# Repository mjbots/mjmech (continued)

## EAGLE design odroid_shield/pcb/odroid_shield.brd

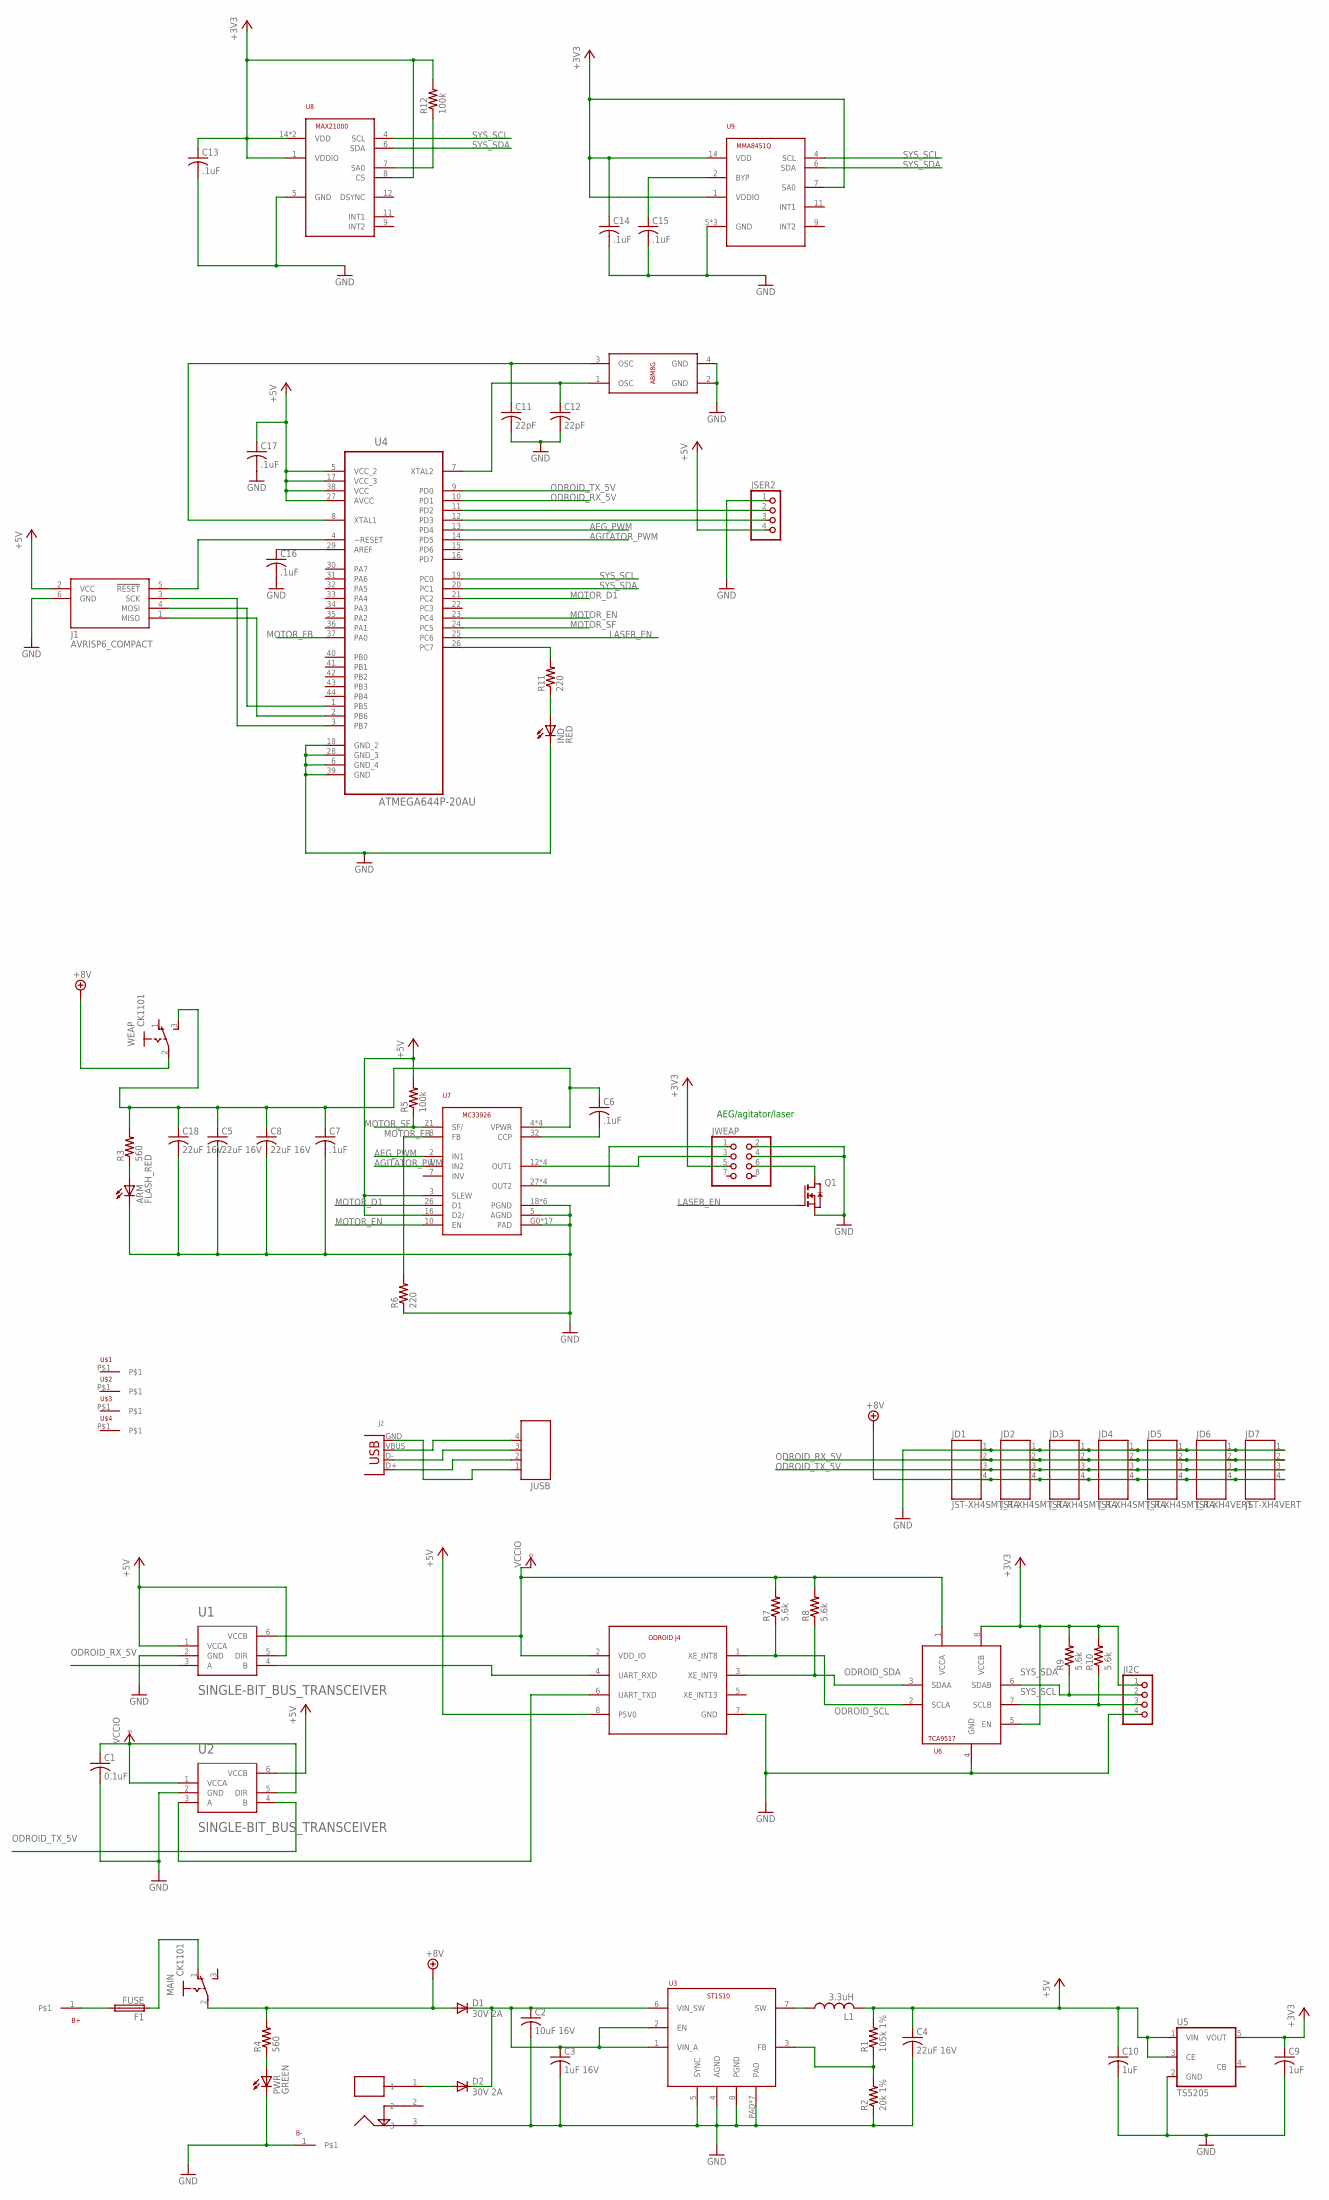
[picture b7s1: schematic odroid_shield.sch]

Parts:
ARM: FLASH_RED; LED5MM
B+: BAT_TERM
B-: BAT_TERM
C1: 0.1uF; C0603
C2: 10uF 16V; C1206
C3: 1uF 16V; C0603
C4, C5, C8, C18: 22uF 16V; C1210
C6, C7, C13, C14, C15, C16, C17: .1uF; C0603
C9, C10: 1uF; C0603
C11, C12: 22pF; C0603
D1, D2: 30V 2A; CMS06
F1: FUSE; KEYSTONE_HORIZ_FUSE_CLIP
IND: RED; CHIPLED_0805
J1: AVRISP6_COMPACT; CON6P2R
J2: USB2MM; 1X04/2MM
J4: ODROID_J4; 2X04/2MM
JD1, JD2, JD3, JD4, JD5: JST-XH4SMT_RA; JST_XH_SMT_RA_4
JD6, JD7: JST-XH4VERT; JST_XH_VERT_4
JI2C: PINHD-1X4; 1X04
JSER2: PINHD-1X4; 1X04
JUSB: JST-PH4
JWEAP: PINHD-2X4; 2X04
L1: 3.3uH; WURTH_74404042033
MAIN: CK1101; CK1101C
PWR: GREEN; CHIPLED_0805
Q1: NMOSSOT23; SOT-23
R1: 105k 1%; R0603
R2: 20k 1%; R0603
R3, R4: 560; R0603
R5, R12: 100k; R0603
R6, R11: 220; R0603
R7, R8, R9, R10: 5.6k; R0603
SHORE: PJ-034ASMT; CUI_PJ_015AH_SMT
U1, U2: SINGLE-BIT_BUS_TRANSCEIVER; SOT23-6
U3: ST1S10; POWER_SO8
U4: ATMEGA644P-20AU; QFP80P1200X1200X120-44N
U5: TS5205; SOT25
U6: TCA9517MSOP8; MSOP8
U7: MC33926; PQFN32
U8: MAX21000; LGA16
U9: MMA8451Q; QFN16
U10: ABM8G
U$1, U$2, U$3, U$4: M3_HEX_MOUNT
WEAP: CK1101; CK1101C

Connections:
+3V3: C9.1, C13.1, C14.1, JI2C.1, JWEAP.5, R9.2, R10.2, R12.2, U5.5 (VOUT), U6.5 (EN), U6.8 (VCCB), U8.1 (VDDIO), U8.8 (CS), U8.14 (VDD), U8.15 (VDD), U9.1 (VDDIO), U9.7 (SA0), U9.14 (VDD)
+5V: C4.1, C10.1, C17.1, J1.2 (VCC), J4.8 (P5V0), JSER2.4, L1.2, R1.2, R5.2, U1.1 (VCCA), U1.5 (DIR), U2.6 (VCCB), U4.5 (VCC_2), U4.17 (VCC_3), U4.27 (AVCC), U4.38 (VCC), U5.1 (VIN), U5.3 (CE), U7.3 (SLEW), U7.16 (D2/)
+8V: D1.1 (A), JD1.4, JD2.4, JD3.4, JD4.4, JD5.4, JD6.4, JD7.4, MAIN.2, R4.2, WEAP.2
AEG_PWM: U4.13 (PD4), U7.2 (IN1)
AGITATOR_PWM: U4.14 (PD5), U7.1 (IN2)
GND: ARM.K (C), B-.1, C1.2, C2.2, C3.2, C4.2, C5.2, C7.2, C8.2, C9.2, C10.2, C11.2, C12.2, C13.2, C14.2, C15.2, C16.2, C17.2, C18.2, IND.C, J1.6 (GND), J4.7 (GND), JD1.1, JD2.1, JD3.1, JD4.1, JD5.1, JD6.1, JD7.1, JI2C.4, JSER2.1, JWEAP.2, JWEAP.4, PWR.C, Q1.2 (S), R2.1, R6.1, SHORE.3, U1.2 (GND), U2.2 (GND), U3.4 (AGND), U3.5 (SYNC), U3.8 (PGND), U3.PAD, U3.PAD1 (PAD), U3.PAD2 (PAD), U3.PAD3 (PAD), U3.PAD4 (PAD), U3.PAD5 (PAD), U3.PAD6 (PAD), U4.6 (GND_4), U4.18 (GND_2), U4.28 (GND_3), U4.39 (GND), U5.2 (GND), U6.4 (GND), U7.5 (AGND), U7.18 (PGND), U7.19 (PGND), U7.20 (PGND), U7.22 (PGND), U7.23 (PGND), U7.24 (PGND), U7.G0 (PAD), U7.G1 (PAD), U7.G2 (PAD), U7.G3 (PAD), U7.G4 (PAD), U7.G5 (PAD), U7.G6 (PAD), U7.G7 (PAD), U7.G8 (PAD), U7.G9 (PAD), U7.G10 (PAD), U7.G11 (PAD), U7.G12 (PAD), U7.G13 (PAD), U7.G14 (PAD), U7.G15 (PAD), U7.G16 (PAD), U8.5 (GND), U9.5 (GND), U9.10 (GND), U9.12 (GND), U10.2 (GND), U10.4 (GND)
LASER_EN: Q1.3 (G), U4.25 (PC6)
MOTOR_D1: U4.21 (PC2), U7.26 (D1)
MOTOR_EN: U4.23 (PC4), U7.10 (EN)
MOTOR_FB: R6.2, U4.37 (PA0), U7.8 (FB)
MOTOR_SF: R5.1, U4.24 (PC5), U7.21 (SF/)
unnamed: J2.VBUS, JUSB.4
unnamed: J4.4 (UART_RXD), U1.4 (B)
unnamed: J2.D-, JUSB.3
unnamed: J4.6 (UART_TXD), U2.3 (A)
unnamed: J2.D+, JUSB.2
unnamed: J2.GND, JUSB.1
unnamed: B+.1, F1.3 (2), F1.4 (2)
unnamed: F1.1, F1.2 (1), MAIN.1 (O)
unnamed: D2.1 (A), SHORE.1
unnamed: L1.1, U3.7 (SW)
unnamed: C2.1, C3.1, D1.2 (C), D2.2 (C), U3.1 (VIN_A), U3.2 (EN), U3.6 (VIN_SW)
unnamed: JWEAP.1, U7.27 (OUT2), U7.28 (OUT2), U7.29 (OUT2), U7.30 (OUT2)
unnamed: R1.1, R2.2, U3.3 (FB)
unnamed: JWEAP.3, U7.12 (OUT1), U7.13 (OUT1), U7.14 (OUT1), U7.15 (OUT1)
unnamed: C5.1, C6.1, C7.1, C8.1, C18.1, R3.2, U7.4 (VPWR), U7.6 (VPWR), U7.11 (VPWR), U7.31 (VPWR), WEAP.3 (S)
unnamed: C6.2, U7.32 (CCP)
unnamed: R11.2, U4.26 (PC7)
unnamed: R12.1, U8.7 (SA0)
unnamed: JWEAP.6, Q1.1 (D)
unnamed: ARM.A, R3.1
unnamed: J1.5 (!RESET), U4.4 (~RESET)
unnamed: PWR.A, R4.1
unnamed: J1.3 (SCK), U4.3 (PB7)
unnamed: J1.4 (MOSI), U4.1 (PB5)
unnamed: J1.1 (MISO), U4.2 (PB6)
unnamed: JSER2.3, U4.12 (PD3)
unnamed: JSER2.2, U4.11 (PD2)
unnamed: IND.A, R11.1
unnamed: C16.1, U4.29 (AREF)
unnamed: C12.1, U4.7 (XTAL2), U10.1 (OSC)
unnamed: C11.1, U4.8 (XTAL1), U10.3 (OSC)
unnamed: C15.1, U9.2 (BYP)
ODROID_RX_5V: JD1.2, JD2.2, JD3.2, JD4.2, JD5.2, JD6.2, JD7.2, U1.3 (A), U4.10 (PD1)
ODROID_SCL: J4.1 (XE_INT8), R7.1, U6.2 (SCLA)
ODROID_SDA: J4.3 (XE_INT9), R8.1, U6.3 (SDAA)
ODROID_TX_5V: JD1.3, JD2.3, JD3.3, JD4.3, JD5.3, JD6.3, JD7.3, U2.4 (B), U4.9 (PD0)
SYS_SCL: JI2C.3, R10.1, U4.19 (PC0), U6.7 (SCLB), U8.4 (SCL), U9.4 (SCL)
SYS_SDA: JI2C.2, R9.1, U4.20 (PC1), U6.6 (SDAB), U8.6 (SDA), U9.6 (SDA)
VCCIO: C1.1, J4.2 (VDD_IO), R7.2, R8.2, U1.6 (VCCB), U2.1 (VCCA), U2.5 (DIR), U6.1 (VCCA)

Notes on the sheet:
AEG/agitator/laser

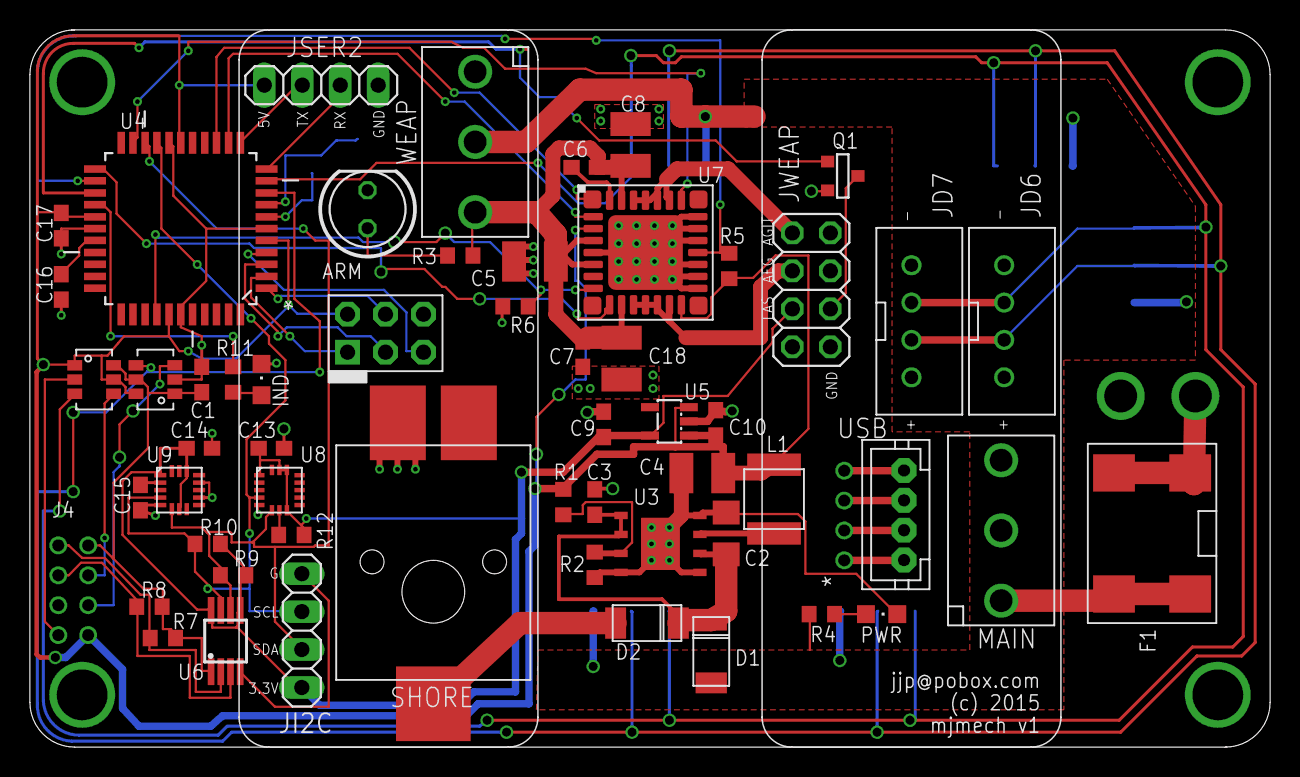
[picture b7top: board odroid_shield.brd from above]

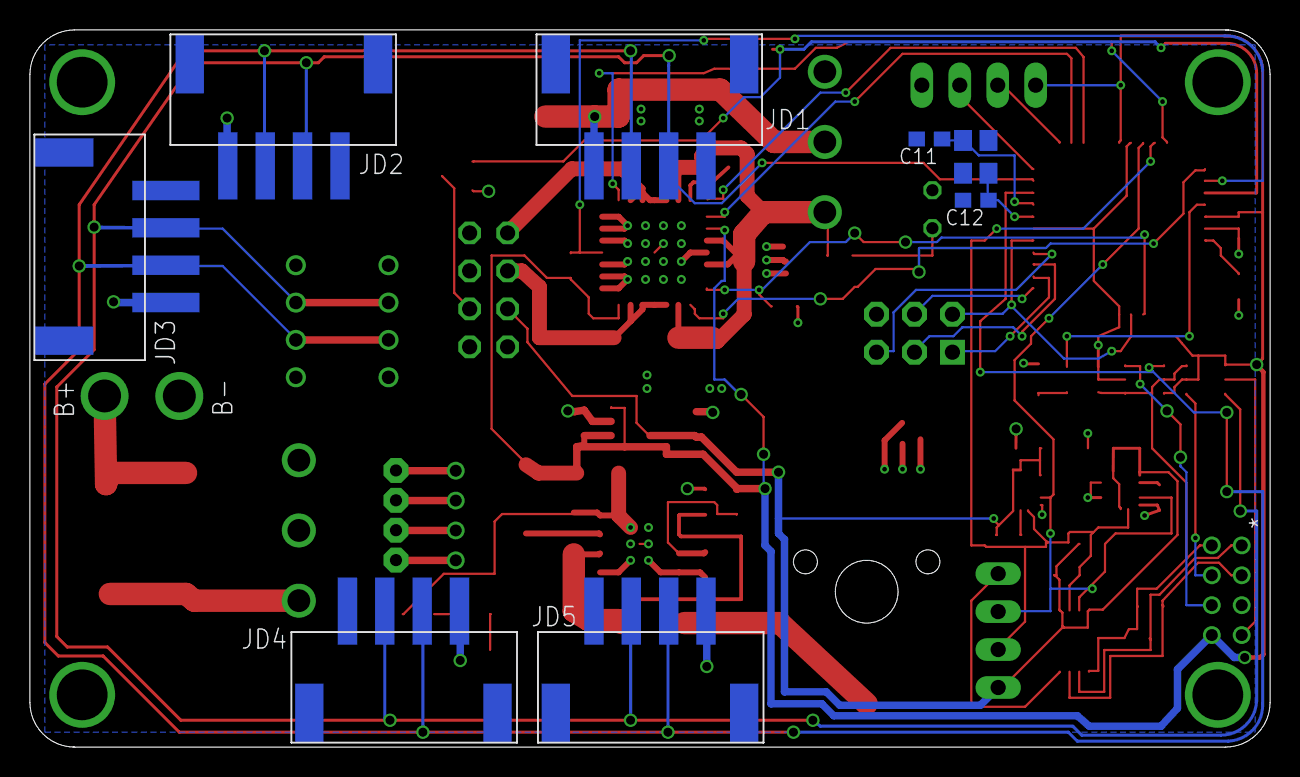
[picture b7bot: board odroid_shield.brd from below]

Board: 2 copper layers, 83.0 x 48.0 mm, 71 parts (11 on the bottom side), 50 nets.

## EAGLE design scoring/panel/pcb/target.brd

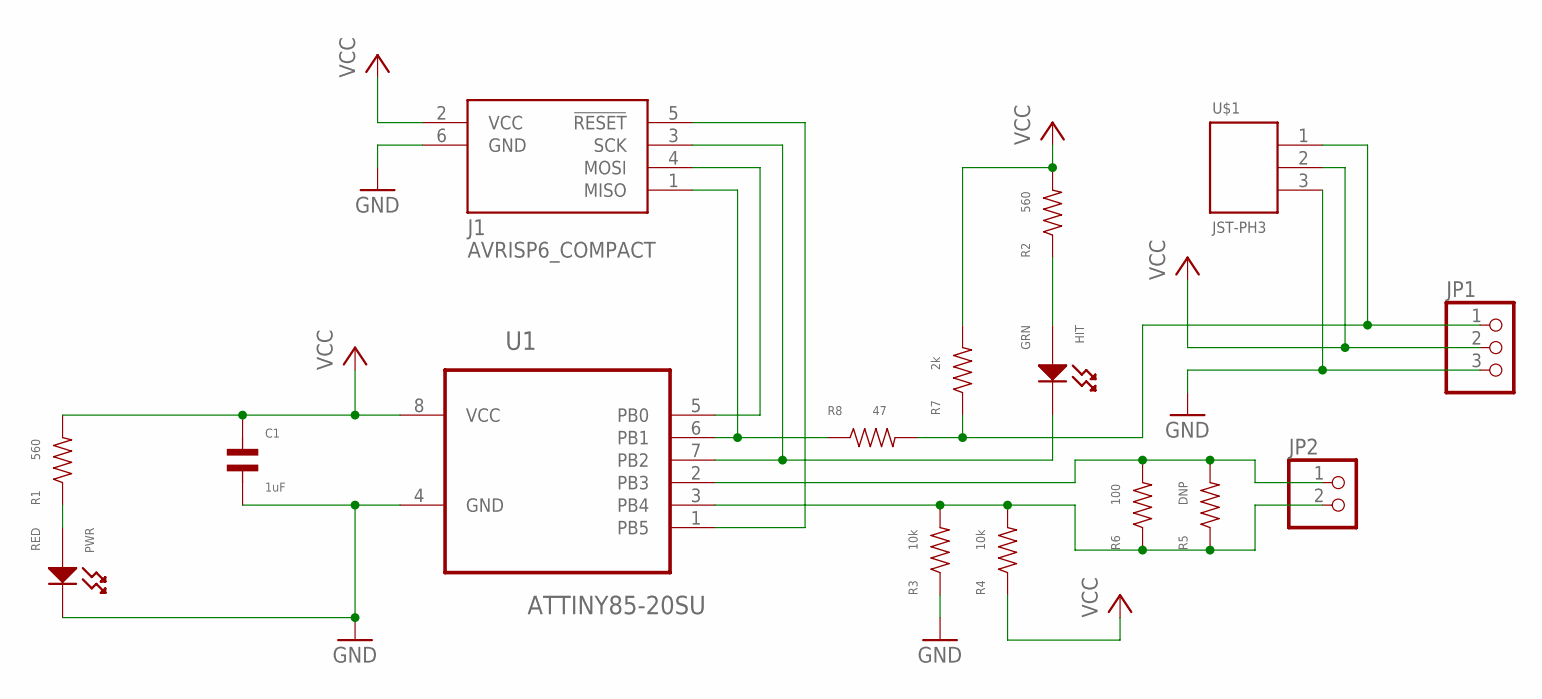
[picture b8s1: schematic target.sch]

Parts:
C1: 1uF; C0603
HIT: GRN; LED0603
J1: AVRISP6_COMPACT; CON6P2R
JP1: PINHD-1X3; 1X03
JP2: PINHD-1X2; 1X02
PWR: RED; LED0603
R1, R2: 560; R0603
R3, R4: 10k; R0603
R5: DNP; R0603
R6: 100; R0603
R7: 2k; R0603
R8: 47; R0603
U1: ATTINY85-20SU; SOIC127P798X216-8N
U$1: JST-PH3

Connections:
GND: C1.P$2, J1.6 (GND), JP1.3, PWR.CATHODE, R3.P$1, U1.4 (GND), U$1.3
unnamed: PWR.ANODE, R1.P$1
unnamed: J1.5 (!RESET), U1.1 (PB5)
unnamed: JP2.2, R3.P$2, R4.P$2, R5.P$1, R6.P$1, U1.3 (PB4)
unnamed: HIT.CATHODE, J1.3 (SCK), U1.7 (PB2)
unnamed: HIT.ANODE, R2.P$1
unnamed: JP2.1, R5.P$2, R6.P$2, U1.2 (PB3)
unnamed: J1.4 (MOSI), U1.5 (PB0)
unnamed: JP1.1, R7.P$1, R8.P$2, U$1.1
unnamed: J1.1 (MISO), R8.P$1, U1.6 (PB1)
VCC: C1.P$1, J1.2 (VCC), JP1.2, R1.P$2, R2.P$2, R4.P$1, R7.P$2, U1.8 (VCC), U$1.2

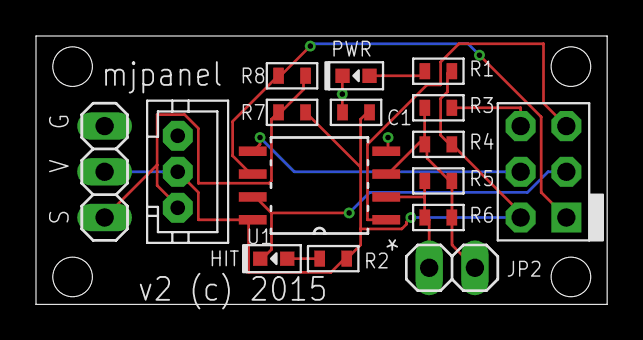
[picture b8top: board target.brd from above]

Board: 2 copper layers, 31.7 x 14.9 mm, 16 parts (0 on the bottom side), 11 nets.

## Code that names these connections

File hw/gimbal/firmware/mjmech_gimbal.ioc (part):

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Mcu.Name=STM32F411R(C-E)Tx
Mcu.Package=LQFP64
Mcu.UserName=STM32F411RETx
PA0-WKUP.Signal=S_TIM2_CH1_ETR
PA1.Signal=S_TIM2_CH2
PA10.Signal=GPIO_Output
PA11.Mode=Device_Only
PA11.Signal=USB_OTG_FS_DM
PA12.Mode=Device_Only
PA12.Signal=USB_OTG_FS_DP
PA13.Mode=Serial-Wire
PA13.Signal=SYS_JTMS-SWDIO
PA14.Mode=Serial-Wire
PA14.Signal=SYS_JTCK-SWCLK
PA15.Signal=GPIO_Input
PA2.Signal=S_TIM2_CH3
PA5.Signal=GPIO_Input
PA6.Signal=GPIO_Output
PA7.Signal=GPIO_Output
PA8.Mode=I2C
PA8.Signal=I2C3_SCL
PA9.Mode=Activate_VBUS
PA9.Signal=USB_OTG_FS_VBUS
PB0.Signal=S_TIM3_CH3
PB1.Signal=S_TIM3_CH4
PB10.Mode=I2C
PB10.Signal=I2C2_SCL
PB12.Signal=GPIO_Output
PB13.Signal=GPIO_Output
PB14.Signal=GPIO_Output
PB15.Signal=GPIO_Output
PB4.Signal=S_TIM3_CH1
PB5.Signal=S_TIM3_CH2
PB6.Mode=I2C
PB6.Signal=I2C1_SCL
PB7.Mode=I2C
PB7.Signal=I2C1_SDA
PB8.Signal=S_TIM4_CH3
PB9.Mode=I2C
PB9.Signal=I2C2_SDA
PC0.Signal=ADCx_IN10
PC1.Signal=ADCx_IN11
PC10.Mode=Full_Duplex_Master
PC10.Signal=SPI3_SCK
PC11.Mode=Full_Duplex_Master
PC11.Signal=SPI3_MISO
PC12.Mode=Full_Duplex_Master
PC12.Signal=SPI3_MOSI
PC13-ANTI_TAMP.Signal=GPIO_Output
PC14-OSC32_IN.Signal=GPIO_Output
PC15-OSC32_OUT.Signal=GPIO_Output
PC2.Signal=ADCx_IN12
PC3.Signal=GPIO_Output
PC6.Mode=Asynchronous
PC6.Signal=USART6_TX
PC7.Mode=Asynchronous
PC7.Signal=USART6_RX
PC9.Mode=I2C
PC9.Signal=I2C3_SDA
PD2.Signal=GPIO_Input
PH0\ -\ OSC_IN.Mode=HSE-External-Oscillator
PH0\ -\ OSC_IN.Signal=RCC_OSC_IN
PH1\ -\ OSC_OUT.Mode=HSE-External-Oscillator
PH1\ -\ OSC_OUT.Signal=RCC_OSC_OUT
RCC.HSE_VALUE=8000000
RCC.SYSCLKFreq_VALUE=96000000
RCC.SYSCLKSource=RCC_SYSCLKSOURCE_PLLCLK
board=mjmech_gimbal

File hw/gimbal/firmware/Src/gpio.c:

/**
  ******************************************************************************
  * File Name          : gpio.c
  * Description        : This file provides code for the configuration
  *                      of all used GPIO pins.
  ******************************************************************************
  *
  * COPYRIGHT(c) 2015 STMicroelectronics
  *
  * Redistribution and use in source and binary forms, with or without modification,
  * are permitted provided that the following conditions are met:
  *   1. Redistributions of source code must retain the above copyright notice,
  *      this list of conditions and the following disclaimer.
  *   2. Redistributions in binary form must reproduce the above copyright notice,
  *      this list of conditions and the following disclaimer in the documentation
  *      and/or other materials provided with the distribution.
  *   3. Neither the name of STMicroelectronics nor the names of its contributors
  *      may be used to endorse or promote products derived from this software
  *      without specific prior written permission.
  *
  * THIS SOFTWARE IS PROVIDED BY THE COPYRIGHT HOLDERS AND CONTRIBUTORS "AS IS"
  * AND ANY EXPRESS OR IMPLIED WARRANTIES, INCLUDING, BUT NOT LIMITED TO, THE
  * IMPLIED WARRANTIES OF MERCHANTABILITY AND FITNESS FOR A PARTICULAR PURPOSE ARE
  * DISCLAIMED. IN NO EVENT SHALL THE COPYRIGHT HOLDER OR CONTRIBUTORS BE LIABLE
  * FOR ANY DIRECT, INDIRECT, INCIDENTAL, SPECIAL, EXEMPLARY, OR CONSEQUENTIAL
  * DAMAGES (INCLUDING, BUT NOT LIMITED TO, PROCUREMENT OF SUBSTITUTE GOODS OR
  * SERVICES; LOSS OF USE, DATA, OR PROFITS; OR BUSINESS INTERRUPTION) HOWEVER
  * CAUSED AND ON ANY THEORY OF LIABILITY, WHETHER IN CONTRACT, STRICT LIABILITY,
  * OR TORT (INCLUDING NEGLIGENCE OR OTHERWISE) ARISING IN ANY WAY OUT OF THE USE
  * OF THIS SOFTWARE, EVEN IF ADVISED OF THE POSSIBILITY OF SUCH DAMAGE.
  *
  ******************************************************************************
  */

/* Includes ------------------------------------------------------------------*/
#include "gpio.h"
/* USER CODE BEGIN 0 */

/* USER CODE END 0 */

/*----------------------------------------------------------------------------*/
/* Configure GPIO                                                             */
/*----------------------------------------------------------------------------*/
/* USER CODE BEGIN 1 */

/* USER CODE END 1 */

/** Configure pins as
        * Analog
        * Input
        * Output
        * EVENT_OUT
        * EXTI
        * Free pins are configured automatically as Analog (this feature is enabled through
        * the Code Generation settings)
*/
void MX_GPIO_Init(void)
{

  GPIO_InitTypeDef GPIO_InitStruct;

  /* GPIO Ports Clock Enable */
  __GPIOC_CLK_ENABLE();
  __GPIOH_CLK_ENABLE();
  __GPIOA_CLK_ENABLE();
  __GPIOB_CLK_ENABLE();
  __GPIOD_CLK_ENABLE();

  /*Configure GPIO pins : PC13 PC14 PC15 PC3 */
  GPIO_InitStruct.Pin = GPIO_PIN_13|GPIO_PIN_14|GPIO_PIN_15|GPIO_PIN_3;
  GPIO_InitStruct.Mode = GPIO_MODE_OUTPUT_PP;
  GPIO_InitStruct.Pull = GPIO_NOPULL;
  GPIO_InitStruct.Speed = GPIO_SPEED_LOW;
  HAL_GPIO_Init(GPIOC, &GPIO_InitStruct);

  /*Configure GPIO pins : PA3 PA4 */
  GPIO_InitStruct.Pin = GPIO_PIN_3|GPIO_PIN_4;
  GPIO_InitStruct.Mode = GPIO_MODE_ANALOG;
  GPIO_InitStruct.Pull = GPIO_NOPULL;
  HAL_GPIO_Init(GPIOA, &GPIO_InitStruct);

  /*Configure GPIO pins : PA5 PA15 */
  GPIO_InitStruct.Pin = GPIO_PIN_5|GPIO_PIN_15;
  GPIO_InitStruct.Mode = GPIO_MODE_INPUT;
  GPIO_InitStruct.Pull = GPIO_NOPULL;
  HAL_GPIO_Init(GPIOA, &GPIO_InitStruct);

  /*Configure GPIO pins : PA6 PA7 PA10 */
  GPIO_InitStruct.Pin = GPIO_PIN_6|GPIO_PIN_7|GPIO_PIN_10;
  GPIO_InitStruct.Mode = GPIO_MODE_OUTPUT_PP;
  GPIO_InitStruct.Pull = GPIO_NOPULL;
  GPIO_InitStruct.Speed = GPIO_SPEED_LOW;
  HAL_GPIO_Init(GPIOA, &GPIO_InitStruct);

  /*Configure GPIO pins : PC4 PC5 PC8 */
  GPIO_InitStruct.Pin = GPIO_PIN_4|GPIO_PIN_5|GPIO_PIN_8;
  GPIO_InitStruct.Mode = GPIO_MODE_ANALOG;
  GPIO_InitStruct.Pull = GPIO_NOPULL;
  HAL_GPIO_Init(GPIOC, &GPIO_InitStruct);

  /*Configure GPIO pins : PB2 PB3 */
  GPIO_InitStruct.Pin = GPIO_PIN_2|GPIO_PIN_3;
  GPIO_InitStruct.Mode = GPIO_MODE_ANALOG;
  GPIO_InitStruct.Pull = GPIO_NOPULL;
  HAL_GPIO_Init(GPIOB, &GPIO_InitStruct);

  /*Configure GPIO pins : PB12 */
  GPIO_InitStruct.Pin = GPIO_PIN_12;
  GPIO_InitStruct.Mode = GPIO_MODE_INPUT;
  GPIO_InitStruct.Pull = GPIO_NOPULL;
  HAL_GPIO_Init(GPIOB, &GPIO_InitStruct);

  /*Configure GPIO pins : PB13 PB14 PB15 */
  GPIO_InitStruct.Pin = GPIO_PIN_12|GPIO_PIN_13|GPIO_PIN_14|GPIO_PIN_15;
  GPIO_InitStruct.Mode = GPIO_MODE_OUTPUT_PP;
  GPIO_InitStruct.Pull = GPIO_NOPULL;
  GPIO_InitStruct.Speed = GPIO_SPEED_LOW;
  HAL_GPIO_Init(GPIOB, &GPIO_InitStruct);

  /*Configure GPIO pin : PD2 */
  GPIO_InitStruct.Pin = GPIO_PIN_2;
  GPIO_InitStruct.Mode = GPIO_MODE_INPUT;
  GPIO_InitStruct.Pull = GPIO_NOPULL;
  HAL_GPIO_Init(GPIOD, &GPIO_InitStruct);

#ifdef MJMECH_DISCOVERY
  /* NOTE jpieper: These pins don't exist on the gimbal board, but are
   * connected to the LEDS on the ST discovery board. */
  GPIO_InitStruct.Pin = GPIO_PIN_12|GPIO_PIN_13|GPIO_PIN_14|GPIO_PIN_15;
  GPIO_InitStruct.Mode = GPIO_MODE_OUTPUT_PP;
  GPIO_InitStruct.Pull = GPIO_NOPULL;
  GPIO_InitStruct.Speed = GPIO_SPEED_LOW;
  HAL_GPIO_Init(GPIOD, &GPIO_InitStruct);
#endif

}

/* USER CODE BEGIN 2 */

/* USER CODE END 2 */

/**
  * @}
  */

/**
  * @}
  */

/************************ (C) COPYRIGHT STMicroelectronics *****END OF FILE****/

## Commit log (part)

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2020-04-01 Measure and report some crude metric of signal strength
2020-04-02 Display telemetry and implement minimal joystick mode
2020-04-02 Improve gait transitions
    Now, we can enter any of rest, walk, or jump, in a relatively clean
    way from the others. Leaving walk we wait for 2 gait cycles with 0
    speed.
    Update rf_command to fill in the repeat and acceleration fields so
    that jumping actually works.
2020-04-02 Make ffmpeg test actually run something
2020-04-03 Report back EAGAIN while reading
2020-04-03 Integrate video rendering into rf_command
2020-04-06 simulator: Use debug time and run at full rate
2020-04-07 Random guessing tweaks to mass and inertia
2020-04-07 Improve the jumping heuristics
    Now, we reliably switch to landing mode shortly after touching the
    ground, since we just look for displacement instead of velocity.
    Also, continually calculate a trajectory when landing so we
    semi-accurately approach the bottom of the jump. This still doesn't
    work all that well yet, so impose a minimum downward velocity also.
2020-04-16 Update config and simulator to new leg geometry
    Not built on robot yet!
2020-04-16 Stub of backflip mode
2020-04-17 aeg_driver: Route most power/gnd
2020-04-17 aeg_driver: Curate BOM
2020-04-25 Move the old turret files out of the way for now
2020-04-25 Many random 3d files for turret
2020-04-25 setup-system: Setup isolcpus and a unique SSID
2020-04-25 The very beginnings of a push stage
2020-04-25 Copy-pasta enough to record the IMU
2020-04-26 Connect up timing measurement in the turret
2020-04-26 Support changing the sign of the servos
2020-04-26 Connect up a rudimentary web_control
2020-04-26 Request higher precision info from servos
2020-04-26 Send always stopped control commands
2020-04-26 Update mjlib
2020-04-27 Beginnings of RF support for the turret
2020-04-27 Actually report the timestamp again
    This was broken by 50a5ad5443fe305bfe79968b803bc44f36e4da29
2020-04-28 Provide a cmline option to scale the max torque for each joint
2020-04-30 More turret prints
2020-04-30 Include screen in the set of utilities
2020-04-30 rf_command: Support rotating the video
2020-05-01 Limit the pitch based on the servo readout
2020-05-01 Incorporate raspicam
2020-05-01 Stub of a raspicam based camera driver
2020-05-01 Basic target tracking
2020-05-03 More turret hw
2020-05-04 Automatically start the turret software in a screen session
2020-05-04 Make the jump acceleration configurable
2020-05-04 Random turret 3d print change
2020-05-05 Use a non-linear control mapping for turret rate
2020-05-05 Tweak yaw gains
2020-05-05 Support multiple overlapping configuration files
2020-05-06 Convert quaternions back into Eigen versions
2020-05-07 Make balance use force control for stance legs
2020-05-07 Add a draft mech warfare config
2020-05-09 Switch to the docking branch of imgui
2020-05-09 tplot2: Implement arrays
2020-05-09 tplot2: Fix seeking
    Turns out std::map::insert doesn't overwrite.
2020-05-09 Make local_override work for github_archive when a `build_file` is present
2020-05-10 tplot2: Add the ability to remove plots
2020-05-10 Render unset optionals as disconnected
2020-05-10 tplot2: Set properties of individual plots
2020-05-11 Update implot
2020-05-11 Enable 32 bit indices in imgui so big plots will work
2020-05-11 Support extracting the GL texture ID
2020-05-11 Proof of concept video rendering
2020-05-11 Add a utility to align video and log files
2020-05-12 First rendering into a texture
    The triangle is busted currently, but it does at least render
    *something*...
2020-05-13 Get a mouse-based virtual trackball working in the 3d view
2020-05-15 Add lighting and get the depth buffer to work
2020-05-15 Render actual feet
2020-05-15 Update tplot2 TODO
2020-05-15 Make normals on spheres be the correct direction
2020-05-15 Switch to a right handed view coordinate system
    This probably isn't the most elegant way, but it does get the job
    done.
2020-05-15 Render simple lines, so far just the leg velocities
    These are pixel wide lines, which are very hard to see, but will get
    the job done for now.
2020-05-15 Fix some missing includes
2020-05-15 Render the ground and fix attitude transformation
    In the process, move the model transform back into C++ to make it
    easier to ensure the ground is rendered with a known transform in the
    "attitude enabled" case.
2020-05-16 Add an aeg_driver TODO
2020-05-17 Implement firing and laser control for the turret
2020-05-18 Correctly report compilation failures
2020-05-23 Control jump repeat mode through the web UI
2020-05-23 Optionally record camera images to disk
2020-05-23 A balance mode that works at least a little in sim
2020-05-23 Factor out runfiles logic into base/
2020-05-24 Support reticle offsets
2020-05-25 Tweak balance contact detection
2020-05-26 First mostly ugly pass at tree-view only derived fields
2020-05-26 Cross off a TODO
2020-05-27 Correctly calculate velocities while moving
2020-05-27 Require non-empty data
2020-05-27 Make it possible to change pose_mm_RB while walking
2020-05-27 Factor enough stuff out of QuadrupedControl to extract the walk logic
2020-05-28 A random script to test curve construction
2020-05-29 Select swing target using expected velocity rather than current
2020-06-03 Implement a cartesian PD controller for each leg
2020-06-05 Update to stance length we're using now
2020-06-06 Update the config
2020-06-06 Work towards making jump work in the new low-gain world
    It doesn't work great yet on the robot. I think we need feedforward
    accelerations to make tracking work better during retract.
2020-06-07 Make jumping work decently again by fudging the servo gains up
2020-06-08 Update TODOs
2020-06-08 Make transitions between jump and walk work decently again
2020-06-12 Initial conversion to use the new pi3hat firmware and software library
    This still has some performance issues
2020-06-14 Implement tunnel functionality for moteus_tool
2020-06-18 Update mjlib and pi3hat
    This accepts API changes in mjlib that required updating all users of
    multiplex::AsioClient. pi3hat.h now can only be included when
    building for raspberry pi too.
2020-06-21 Remove what's left of legtool
2020-06-21 Log the rpi temperature
2020-06-22 Switch to use double values now that implot supports it
2020-06-22 Allow empty records to be expanded
    Dynamic lists just get an element "0", so not perfect
2020-06-22 Make newly added plots be selected for properties and removal by default
2020-06-22 Persist the mech render check boxes
2020-06-22 Tweak TODO
2020-06-23 Add a notional CoM frame
2020-06-23 Remove QuadrupedDebug... it has been too long since it was used
2020-06-23 Create a class to express the kinematic relation between two rigid bodies
    Use it as the vocabulary type to record our frame relations
2020-06-23 Remove more unused files
2020-06-24 Use the correctly named "M" frame
2020-06-24 Make commanded force rendering work again after cartesian PD control
2020-06-24 Oops, these need to be there to build
2020-06-24 Remove the now unused B_frame option
2020-06-25 Use the correct sense in an assert
2020-06-26 Don't capture a pointer to a pointer by accident
    This is UB, but happens to work in release builds
2020-06-26 Adjust CoM location based on an estimate of the current terrain
    This changes a number of things:
    First, the RB offset is no longer commandable across all gaits. There
    is instead a "rest" only option to add an additional offset to that
    command.
    Second, there is a new "T" frame, which is an estimate of the terrain
    under the robots feet. That is estimated recursively based on feet
2020-06-29 Be slightly smarter about foot lift selection
    Now we calculate a valid region, and force the feet to lift if it
    looks like a leg is going to reach the point where it would otherwise
    go invalid.
2020-07-01 Beginnings of a script to help with improved trot timings
2020-07-03 Update mjlib to get compliant JSON
    Now that we have json and not json5, show that we can actually read
    the data from the javascript code in some minimal way.
2020-07-05 Make qdd100_test actually render data again
2020-07-06 Get the HTML/CSS where I want it, although the JS still is broken
2020-07-06 More web app work
    Scales now auto-populate, and interacting with the graphical command
    expands and collapses the mode expander as appropriate.
2020-07-06 Unless "force step" is checked, stop stepping when no movement commanded
2020-07-06 Implement body mode
2020-07-06 Support changing the movement mode from the joystick
2020-07-06 Only allow one websocket controller at a time
2020-07-09 Update to a moteus_tool which can flash the servos on the pi3hat
2020-07-09 Automatically rezero the servos assuming the "nominal" start position
2020-07-09 Add a new script to configure all the quad A1 servo parameters
    While we are at it, remove a bunch of stale scripts
2020-07-09 When first connecting to the robot, attempt to divine what mode to be in
    This makes it less likely that a spurious network disconnect (or even
    a page reload), would result in the robot falling down.
2020-07-11 Optionall force usage of a specific pi3hat bus
2020-07-12 Display the max joint temperature in the UI
2020-07-13 Add default ssh key and instructions on changing it
2020-07-26 qdd100_test: Optionally report data from a power supply
2020-07-26 Record servo debug information while testing
2020-07-27 Remove some unused docs
2020-07-31 Tool to plot as5047 noise
2020-07-31 tplot2: Don't barf if a restored plot no longer exists
2020-08-01 tplot2: Support toggling rendering of the body
2020-08-03 Initial stub of a telepresence demo
2020-08-03 Minimally working telepresence demo
2020-08-04 Provide buttons to reset to known camera locations
    Also provide a non-functional switch between perspective and ortho modes
2020-08-05 Make the floor bigger still
2020-08-07 Make forward and reverse commands asymmetric
2020-08-16 Whitespace fixes
2020-08-24 Minimal attempt at allocating gravity weight among legs
2020-08-24 Remove the old swing_time constant, replacing it with the new calculated version
2020-08-25 By default, disable strafing
2020-09-01 Only update terrain with feet that are exerting downforce
    This reduces the amount that a bouncing foot can corrupt the estimate
    of terrain.
2020-09-02 Fix typo
2020-09-02 Add one more focal package
2020-09-04 Calculate joint velocities using the current, not ideal positions
    We were already doing this for torque, and it makes sense to do it for
    velocities too. Near extremal positions, the velocities can change
    drastically, which can result in force application in significantly
    the wrong direction.
2020-09-04 Add a double check to prevent negative servo gains
2020-09-05 Max maximum forward speed configurable in the web interface
2020-09-05 Persist the jump acceleration
2020-09-05 When pronking, limit the maximum forward and reverse speed
2020-09-09 Simplify the restorative velocity calculation by saving some state and no longer ramping it down
2020-09-14 Update servo config for newer firmware version
2020-09-16 Don't update terrain when we aren't controlling feet or are in flight
2020-09-21 When in flight phase, use a more robust heuristic for maintaining phase
    Previously we would look at the remaining time in the stance phase.
    However, that is very sensitive to where the feet actually landed.
    Now we just add a correction based on how long it has been since the
    last swing phase started.
2020-10-26 Only allow window dragging from the title bar
2020-10-28 Make Saturate actually correct
2020-11-02 Don't crash if leg_pds isn't present
